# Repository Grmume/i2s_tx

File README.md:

# i2s_tx
Transceiver to transmit i2s over ethernet cable (4 channels per cable, >= Cat5).

The input of this board matches the pinout of the miniDsp Usbstreamer.
It can be used to transmit up to 8 channels of i2s audio over ethernet cable at upto 96 Kbit/s (hopefully). All channels share the same clocks.
Two of the RJ45 sockets have the same channels connected, to be able to have this PCB at the center of a setup and run one cable to the right side and one cable to the left side.

See the i2s_rxtx repository for information on how to receive the signals and convert them back to i2s.

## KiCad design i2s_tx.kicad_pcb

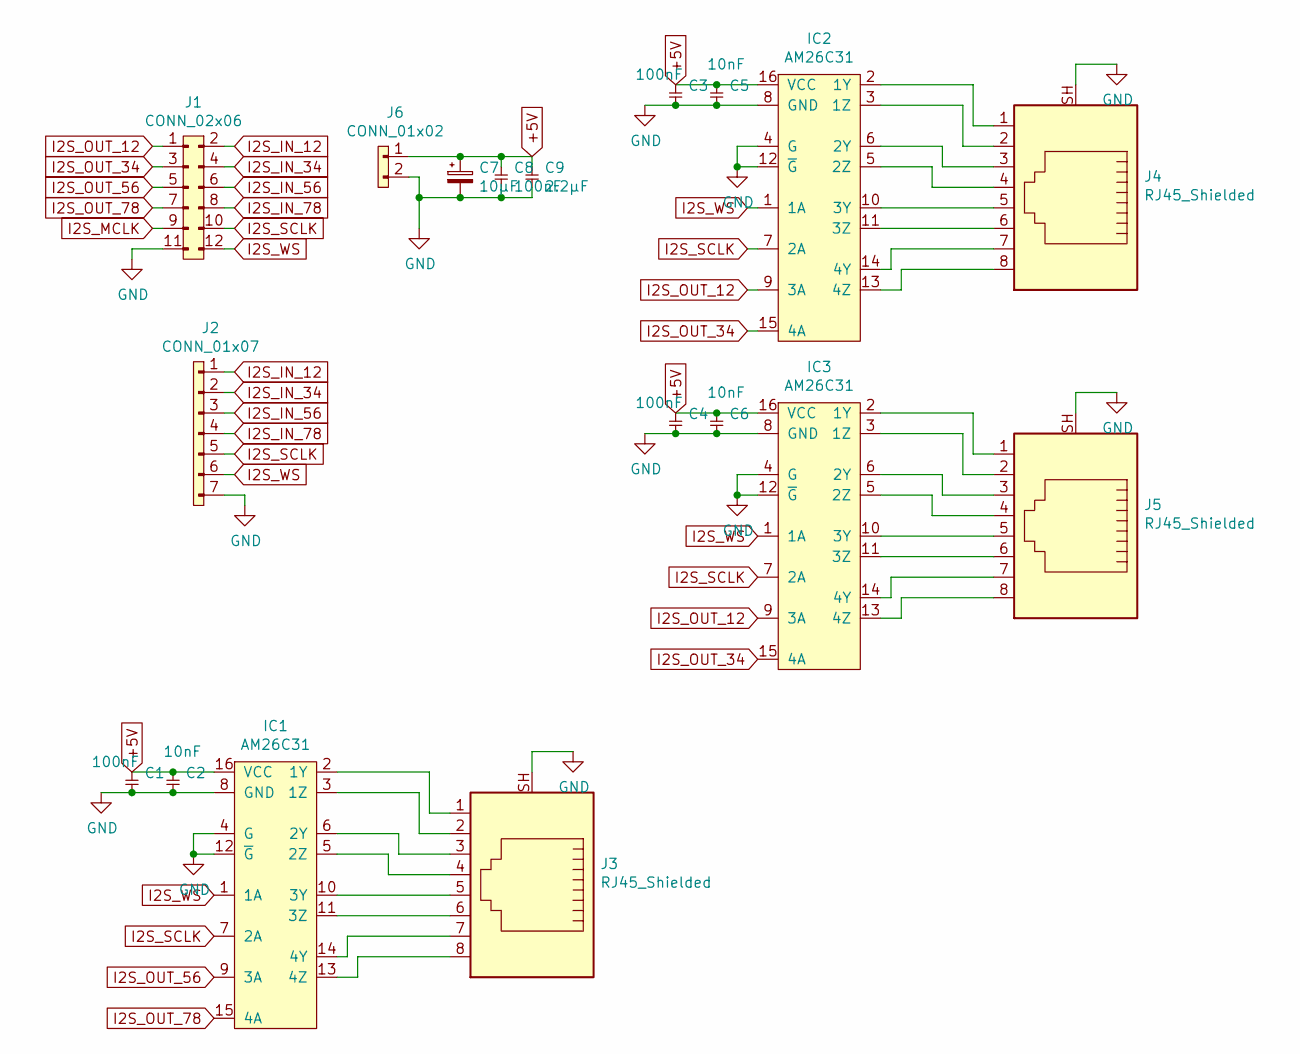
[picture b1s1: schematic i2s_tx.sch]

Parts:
C1, C3, C4, C8: 100nF; C_0805_2012Metric_Pad1.15x1.40mm_HandSolder
C2, C5, C6: 10nF; C_0805_2012Metric_Pad1.15x1.40mm_HandSolder
C7: 10µF; CP_Elec_6.3x5.4
C9: 2.2µF; C_0805_2012Metric_Pad1.15x1.40mm_HandSolder
IC1, IC2, IC3: AM26C31; SOIC-16_3.9x9.9mm_P1.27mm; Farnell 4975637
J1: CONN_02x06; PinHeader_2x06_P2.00mm_Vertical
J2: CONN_01x07; PinHeader_1x07_P2.00mm_Vertical
J3, J4, J5: RJ45_Shielded; RJ45_Weidmueller
J6: CONN_01x02; PinHeader_1x02_P2.00mm_Vertical

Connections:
+5V: C1.1, C2.1, C3.1, C4.1, C5.1, C6.1, C7.1, C8.1, C9.1, IC1.16 (VCC), IC2.16 (VCC), IC3.16 (VCC), J6.1
GND: C1.2, C2.2, C3.2, C4.2, C5.2, C6.2, C7.2, C8.2, C9.2, IC1.4 (G), IC1.8 (GND), IC1.12 (~G), IC2.4 (G), IC2.8 (GND), IC2.12 (~G), IC3.4 (G), IC3.8 (GND), IC3.12 (~G), J1.11, J2.7, J3.SH, J4.SH, J5.SH, J6.2
I2S_IN_12: J1.2, J2.1
I2S_IN_34: J1.4, J2.2
I2S_IN_56: J1.6, J2.3
I2S_IN_78: J1.8, J2.4
I2S_MCLK: J1.9
I2S_OUT_12: IC2.9 (3A), IC3.9 (3A), J1.1
I2S_OUT_34: IC2.15 (4A), IC3.15 (4A), J1.3
I2S_OUT_56: IC1.9 (3A), J1.5
I2S_OUT_78: IC1.15 (4A), J1.7
I2S_SCLK: IC1.7 (2A), IC2.7 (2A), IC3.7 (2A), J1.10, J2.5
I2S_WS: IC1.1 (1A), IC2.1 (1A), IC3.1 (1A), J1.12, J2.6
unnamed: IC1.2 (1Y), J3.1
unnamed: IC1.3 (1Z), J3.2
unnamed: IC1.5 (2Z), J3.4
unnamed: IC1.6 (2Y), J3.3
unnamed: IC1.10 (3Y), J3.5
unnamed: IC1.11 (3Z), J3.6
unnamed: IC1.13 (4Z), J3.8
unnamed: IC1.14 (4Y), J3.7
unnamed: IC2.2 (1Y), J4.1
unnamed: IC2.3 (1Z), J4.2
unnamed: IC2.5 (2Z), J4.4
unnamed: IC2.6 (2Y), J4.3
unnamed: IC2.10 (3Y), J4.5
unnamed: IC2.11 (3Z), J4.6
unnamed: IC2.13 (4Z), J4.8
unnamed: IC2.14 (4Y), J4.7
unnamed: IC3.2 (1Y), J5.1
unnamed: IC3.3 (1Z), J5.2
unnamed: IC3.5 (2Z), J5.4
unnamed: IC3.6 (2Y), J5.3
unnamed: IC3.10 (3Y), J5.5
unnamed: IC3.11 (3Z), J5.6
unnamed: IC3.13 (4Z), J5.8
unnamed: IC3.14 (4Y), J5.7

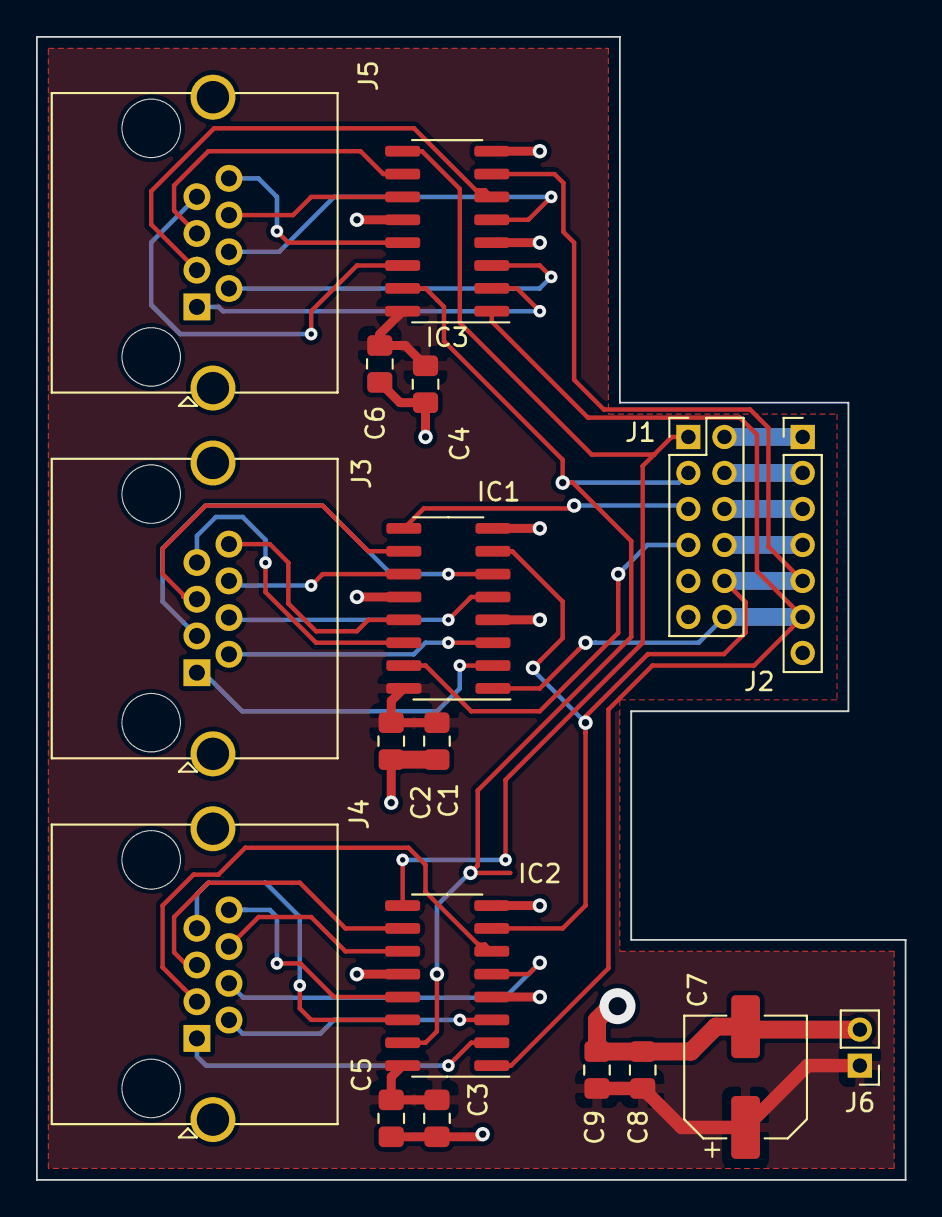
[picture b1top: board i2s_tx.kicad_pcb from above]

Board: 2 copper layers, 48.3 x 63.5 mm, 18 parts (0 on the bottom side), 36 nets.

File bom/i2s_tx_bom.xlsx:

Board | i2s_tx
BOM
References | Value | Footprint | Datasheet | Supplier1 Partnumber | Supplier2 Partnumber | Count | URL Reichelt | Unit Pr. Reichelt
> C1, C3, C4, C8 | 100nF | Capacitor_SMD:C_0805_2012Metric_Pad1.15x1.40mm_HandSolder |  |  |  | 4
> C2, C5, C6 | 10nF | Capacitor_SMD:C_0805_2012Metric_Pad1.15x1.40mm_HandSolder |  |  |  | 3
C7 | 10µF | Capacitor_SMD:CP_Elec_6.3x5.4 | ~ |  |  | 1
C9 | 2.2µF | Capacitor_SMD:C_0805_2012Metric_Pad1.15x1.40mm_HandSolder |  |  |  | 1
> IC1-IC3 | AM26C31 | Package_SO:SOIC-16_3.9x9.9mm_P1.27mm | http://www.ti.com.cn/cn/lit/ds/symlink/am26c31.pdf | 4975637 |  | 3
J1 | CONN_02x06 | Connector_PinHeader_2.00mm:PinHeader_2x06_P2.00mm_Vertical |  |  |  | 1
J2 | CONN_01x07 | Connector_PinHeader_2.00mm:PinHeader_1x07_P2.00mm_Vertical |  |  |  | 1
> J3-J5 | RJ45_Shielded | agg:RJ45_Weidmueller | ~ |  |  | 3
J6 | CONN_01x02 | Connector_PinHeader_2.00mm:PinHeader_1x02_P2.00mm_Vertical |  |  |  | 1

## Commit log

2019-06-03 -- added first version
2019-06-08 -- update
2019-06-16 --updated gerbers
2019-06-16 -- updated vias
2019-06-16 -- updated silkscreen
2019-07-19 -- added bom
